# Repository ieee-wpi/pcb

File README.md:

# Essentials of PCB Design

[![CC BY-SA 4.0][cc-by-sa-shield]][cc-by-sa]

Project-oriented PCB design course taught at WPI. The course is a evening lecture series where students learn to layout and route an embedded system. Students then receive their boards and assemble them. The class was created by [Daniel Gorbunov](https://github.com/dgorbunov) and [Hubert Liu](https://github.com/124274sashimi) in 2024 and has been run every year since through the [IEEE WPI Student Branch](https://ieee.wpi.edu), which helps fund the class. You can reach us at [gr-pcb@wpi.edu](mailto:gr-pcb@wpi.edu) if you have questions.

### Lectures
| #  | Lecture				    |
| -- |-------- 				    |
| 01 | PCB Basics 		    |
| 02 | Project Design     |
| 03 | Layout + Routing   |
| 04 | Working with KiCad |

### Materials
| Folder      	  | Contents		            |
| --          	  |       -------- 			    |
| `datasheets`    | Datasheets for major parts  |
| `sample_board`  | Sample board design         |
| `slides`        | PDFs of slides	          	|
| `starter_board` | Starter template design     | 
| `code`        | Code examples	    |

### Lecture Recordings

> Note: To access the lecture recordings, you must sign in with a WPI account. This is WPI's policy for Echo360 recordings.

| Year  | Term  | Echo360      |
| ----- | ----- | ------------ |
| 2024 | A-Term | [Link](https://echo360.org/collection/4c2d5caf-a301-4c32-a2dd-bdd8c8c0b9d9/public) | 
| 2025 | A-Term | [Link](https://echo360.org/collection/bc2acf2f-69f2-4496-9638-cb1b12c30087/public) |
| 2026 | C-Term | [Link](https://echo360.org/collection/0ecf9c61-5003-4061-9b4f-ee87c14e6741/public) |

## Getting Started
Not sure where to get started on your design? You'll need to download and install [KiCad](https://www.kicad.org/download/). You'll also need the [Arduino IDE](https://www.arduino.cc/en/software) to program your board.

### Board
To get started on your own board design, navigate to [starter_board](https://github.com/IEEE-WPI/pcb/tree/main/starter_board) and read the instructions in the `README` file.

### Code
To get started uploading code to your board, navigate to [code](https://github.com/IEEE-WPI/pcb/tree/main/code) and read the instructions in the `README` file.

## License
This work is licensed under a
[Creative Commons Attribution-ShareAlike 4.0 International License][cc-by-sa].

[![CC BY-SA 4.0][cc-by-sa-image]][cc-by-sa]

[cc-by-sa]: http://creativecommons.org/licenses/by-sa/4.0/
[cc-by-sa-image]: https://licensebuttons.net/l/by-sa/4.0/88x31.png
[cc-by-sa-shield]: https://img.shields.io/badge/License-CC%20BY--SA%204.0-lightgrey.svg

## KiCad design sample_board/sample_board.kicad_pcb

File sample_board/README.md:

## Sample Board
This folder contains the sample board for the Track 1 design. We've ordered these boards to help demonstrate what the Track 1 boards will do. 

**If you're in Track 1, we encourage you not to look at the sample board files, but rather come up with your own layout and routing solutions**. The sample board by no means represents "the best" design for the board.

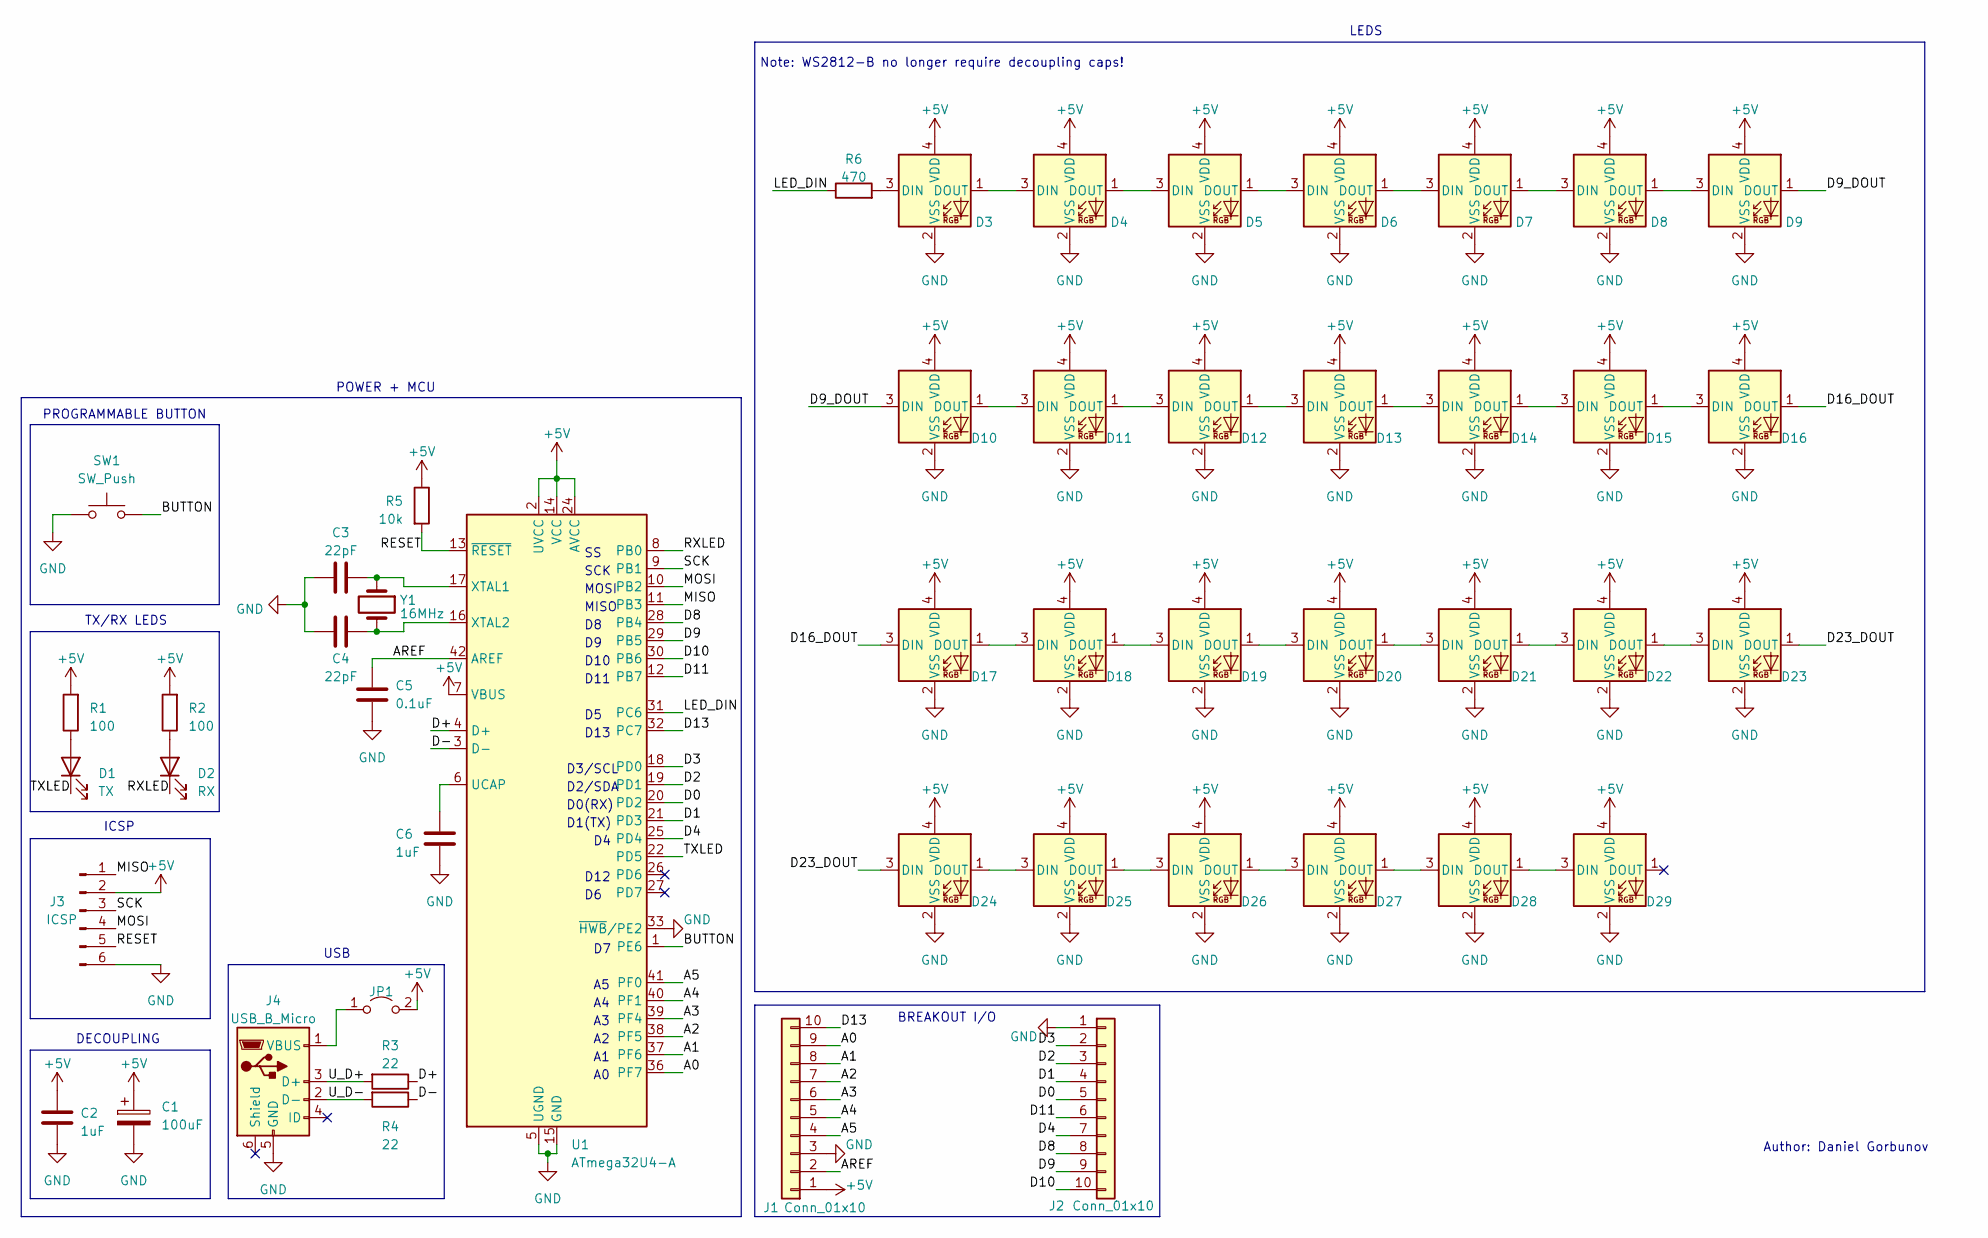
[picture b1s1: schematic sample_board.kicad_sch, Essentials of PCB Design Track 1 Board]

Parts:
C1: 100uF; CP_Elec_5x5.3
C2, C6: 1uF; C_0805_2012Metric_Pad1.18x1.45mm_HandSolder
C3, C4: 22pF; C_0805_2012Metric_Pad1.18x1.45mm_HandSolder
C5: 0.1uF; C_0805_2012Metric_Pad1.18x1.45mm_HandSolder
D1: TX; LED_0805_2012Metric_Pad1.15x1.40mm_HandSolder
D2: RX; LED_0805_2012Metric_Pad1.15x1.40mm_HandSolder
D3, D4, D5, D6, D7, D8, D9, D10, D11, D12, D13, D14, D15, D16, D17, D18, D19, D20, D21, D22, D23, D24, D25, D26, D27, D28, D29: SK6812MINI; LED_SK6812MINI_PLCC4_3.5x3.5mm_P1.75mm
J1, J2: Conn_01x10; PinHeader_1x10_P2.54mm_Vertical
J3: ICSP; PinHeader_2x03_P2.54mm_Vertical
J4: USB_B_Micro; USB_Micro-B_GCT_USB3076-30-A
JP1: Jumper_2_Open; SolderJumper-2_P1.3mm_Open_TrianglePad1.0x1.5mm
R1, R2: 100; R_0805_2012Metric_Pad1.20x1.40mm_HandSolder
R3, R4: 22; R_0805_2012Metric_Pad1.20x1.40mm_HandSolder
R5: 10k; R_0805_2012Metric_Pad1.20x1.40mm_HandSolder
R6: 470; R_0805_2012Metric_Pad1.20x1.40mm_HandSolder
SW1: SW_Push; SW_SPST_PTS647_Sx38
U1: ATmega32U4-A; TQFP-44_10x10mm_P0.8mm
Y1: 16MHz; Crystal_SMD_5032-2Pin_5.0x3.2mm

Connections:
+5V: C1.1, C2.1, D3.4 (VDD), D4.4 (VDD), D5.4 (VDD), D6.4 (VDD), D7.4 (VDD), D8.4 (VDD), D9.4 (VDD), D10.4 (VDD), D11.4 (VDD), D12.4 (VDD), D13.4 (VDD), D14.4 (VDD), D15.4 (VDD), D16.4 (VDD), D17.4 (VDD), D18.4 (VDD), D19.4 (VDD), D20.4 (VDD), D21.4 (VDD), D22.4 (VDD), D23.4 (VDD), D24.4 (VDD), D25.4 (VDD), D26.4 (VDD), D27.4 (VDD), D28.4 (VDD), D29.4 (VDD), J1.1, J3.2, JP1.2 (B), R1.2, R2.2, R5.1, U1.2 (UVCC), U1.7 (VBUS), U1.14 (VCC), U1.24 (AVCC), U1.34 (VCC), U1.44 (AVCC)
/A0: J1.9, U1.36 (PF7)
/A1: J1.8, U1.37 (PF6)
/A2: J1.7, U1.38 (PF5)
/A3: J1.6, U1.39 (PF4)
/A4: J1.5, U1.40 (PF1)
/A5: J1.4, U1.41 (PF0)
/AREF: C5.1, J1.2, U1.42 (AREF)
/BUTTON: SW1.2, U1.1 (PE6)
/D0: J2.5, U1.20 (PD2)
/D1: J2.4, U1.21 (PD3)
/D2: J2.3, U1.19 (PD1)
/D3: J2.2, U1.18 (PD0)
/D4: J2.7, U1.25 (PD4)
/D8: J2.8, U1.28 (PB4)
/D9: J2.9, U1.29 (PB5)
/D9_DOUT: D9.1 (DOUT), D10.3 (DIN)
/D10: J2.10, U1.30 (PB6)
/D11: J2.6, U1.12 (PB7)
/D13: J1.10, U1.32 (PC7)
/D16_DOUT: D16.1 (DOUT), D17.3 (DIN)
/D23_DOUT: D23.1 (DOUT), D24.3 (DIN)
/D+: R3.1, U1.4 (D+)
/D-: R4.1, U1.3 (D-)
/LED_DIN: R6.1, U1.31 (PC6)
/MISO: J3.1, U1.11 (PB3)
/MOSI: J3.4, U1.10 (PB2)
/RESET: J3.5, R5.2, U1.13 (~RESET)
/RXLED: D2.1 (K), U1.8 (PB0)
/SCK: J3.3, U1.9 (PB1)
/TXLED: D1.1 (K), U1.22 (PD5)
/U_D+: J4.3 (D+), R3.2
/U_D-: J4.2 (D-), R4.2
GND: C1.2, C2.2, C3.2, C4.2, C5.2, C6.2, D3.2 (VSS), D4.2 (VSS), D5.2 (VSS), D6.2 (VSS), D7.2 (VSS), D8.2 (VSS), D9.2 (VSS), D10.2 (VSS), D11.2 (VSS), D12.2 (VSS), D13.2 (VSS), D14.2 (VSS), D15.2 (VSS), D16.2 (VSS), D17.2 (VSS), D18.2 (VSS), D19.2 (VSS), D20.2 (VSS), D21.2 (VSS), D22.2 (VSS), D23.2 (VSS), D24.2 (VSS), D25.2 (VSS), D26.2 (VSS), D27.2 (VSS), D28.2 (VSS), D29.2 (VSS), J1.3, J2.1, J3.6, J4.5 (GND), SW1.1, U1.5 (UGND), U1.15 (GND), U1.23 (GND), U1.33 (~HWB/PE2), U1.35 (GND), U1.43 (GND)
unnamed: D1.2 (A), R1.1
unnamed: D2.2 (A), R2.1
unnamed: D3.3 (DIN), R6.2
unnamed: D3.1 (DOUT), D4.3 (DIN)
unnamed: D4.1 (DOUT), D5.3 (DIN)
unnamed: D5.1 (DOUT), D6.3 (DIN)
unnamed: D6.1 (DOUT), D7.3 (DIN)
unnamed: D7.1 (DOUT), D8.3 (DIN)
unnamed: D8.1 (DOUT), D9.3 (DIN)
unnamed: D10.1 (DOUT), D11.3 (DIN)
unnamed: D11.1 (DOUT), D12.3 (DIN)
unnamed: D12.1 (DOUT), D13.3 (DIN)
unnamed: D13.1 (DOUT), D14.3 (DIN)
unnamed: D14.1 (DOUT), D15.3 (DIN)
unnamed: D15.1 (DOUT), D16.3 (DIN)
unnamed: D17.1 (DOUT), D18.3 (DIN)
unnamed: D18.1 (DOUT), D19.3 (DIN)
unnamed: D19.1 (DOUT), D20.3 (DIN)
unnamed: D20.1 (DOUT), D21.3 (DIN)
unnamed: D21.1 (DOUT), D22.3 (DIN)
unnamed: D22.1 (DOUT), D23.3 (DIN)
unnamed: D24.1 (DOUT), D25.3 (DIN)
unnamed: D25.1 (DOUT), D26.3 (DIN)
unnamed: D26.1 (DOUT), D27.3 (DIN)
unnamed: D27.1 (DOUT), D28.3 (DIN)
unnamed: D28.1 (DOUT), D29.3 (DIN)
unnamed: J4.1 (VBUS), JP1.1 (A)
unnamed: C6.1, U1.6 (UCAP)
unnamed: C3.1, U1.17 (XTAL1), Y1.1
unnamed: C4.1, U1.16 (XTAL2), Y1.2

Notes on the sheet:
MOSI
D2/SDA
LEDS
D11
D3/SCL
USB
DECOUPLING
D1(TX)
D13
Note: WS2812-B no longer require decoupling caps!
Author: Daniel Gorbunov
PROGRAMMABLE BUTTON
MISO
D10
BREAKOUT I/O
POWER + MCU
TX/RX LEDS
ICSP
SCK
D12
D0(RX)

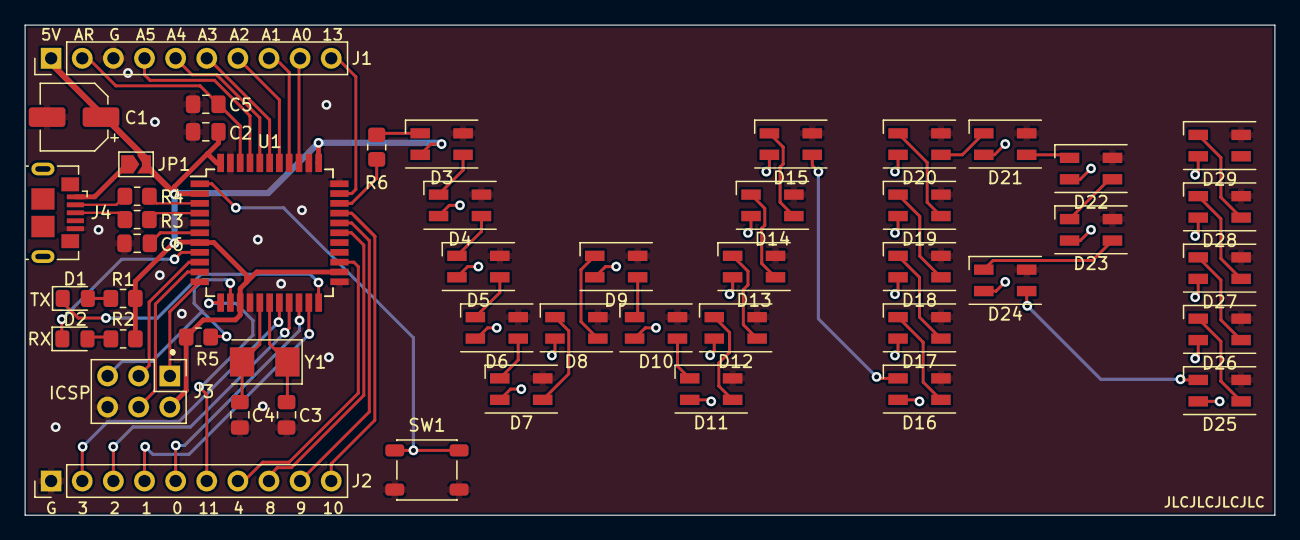
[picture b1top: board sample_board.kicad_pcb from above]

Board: 2 copper layers, 102.0 x 40.0 mm, 49 parts (0 on the bottom side), 64 nets.

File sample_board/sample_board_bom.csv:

"#","Reference","Qty","Value","Footprint","DNP"
"1","C1","1","100uF","Capacitor_SMD:CP_Elec_5x5.3",""
"2","C2, C6","2","1uF","Capacitor_SMD:C_0805_2012Metric_Pad1.18x1.45mm_HandSolder",""
"3","C3, C4","2","22pF","Capacitor_SMD:C_0805_2012Metric_Pad1.18x1.45mm_HandSolder",""
"4","C5","1","0.1uF","Capacitor_SMD:C_0805_2012Metric_Pad1.18x1.45mm_HandSolder",""
"5","D1","1","TX","LED_SMD:LED_0805_2012Metric_Pad1.15x1.40mm_HandSolder",""
"6","D2","1","RX","LED_SMD:LED_0805_2012Metric_Pad1.15x1.40mm_HandSolder",""
"7","D3, D4, D5, D6, D7, D8, D9, D10, D11, D12, D13, D14, D15, D16, D17, D18, D19, D20, D21, D22, D23, D24, D25, D26, D27, D28, D29","27","SK6812MINI","LED_SMD:LED_SK6812MINI_PLCC4_3.5x3.5mm_P1.75mm",""
"8","J1, J2","2","Conn_01x10","Connector_PinHeader_2.54mm:PinHeader_1x10_P2.54mm_Vertical",""
"9","J3","1","ICSP","Connector_PinHeader_2.54mm:PinHeader_2x03_P2.54mm_Vertical",""
"10","J4","1","USB_B_Micro","Connector_USB:USB_Micro-B_GCT_USB3076-30-A",""
"11","JP1","1","Jumper_2_Open","Jumper:SolderJumper-2_P1.3mm_Open_TrianglePad1.0x1.5mm",""
"12","R1, R2","2","100","Resistor_SMD:R_0805_2012Metric_Pad1.20x1.40mm_HandSolder",""
"13","R3, R4","2","22","Resistor_SMD:R_0805_2012Metric_Pad1.20x1.40mm_HandSolder",""
"14","R5","1","10k","Resistor_SMD:R_0805_2012Metric_Pad1.20x1.40mm_HandSolder",""
"15","R6","1","470","Resistor_SMD:R_0805_2012Metric_Pad1.20x1.40mm_HandSolder",""
"16","U1","1","ATmega32U4-A","Package_QFP:TQFP-44_10x10mm_P0.8mm",""
"17","Y1","1","16MHz","Crystal:Crystal_SMD_5032-2Pin_5.0x3.2mm",""

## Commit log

2024-09-21 move repo to org
2024-09-24 a-term lecture 1 slides
2024-09-24 cleanup stray gerber files
2024-09-25 cleanup
2024-09-25 reorg and update readme
2024-09-26 untrack kicad cache files
2024-09-26 add datasheets and new sample board files
2024-09-26 remove cached starter board files
2024-09-26 update board files for A24
2024-09-26 add d24 gerbers and update readme
2024-09-26 add design slides
2024-09-27 add gerbers
2024-09-27 update design slide with fixed image
2024-10-01 add READMEs to all folders
2024-10-01 update root readme with links
2024-10-01 fix readme links again
2024-10-01 add sample board readme
2024-10-01 update root README with starter links
2024-10-01 update starter code
2024-10-01 lock components
2024-10-01 layout and routing slides
2024-10-03 updated 3rd and 4th lecture slides
2024-10-06 sample board rev2; added button
2024-10-25 update lecture names in readme
2024-10-26 regenerate gerbers
2024-10-26 restore d24 board
2024-10-26 add colorful silkscreen board
2024-11-08 update flashlight code and add strobe
2024-12-08 Add CC license to README
2025-09-23 Add 2025 basics slides
2025-09-25 Add updated slides
2025-10-01 Add lecture 3 slides
2025-10-02 Add lecture 4 slides
2025-10-02 Add updated term to board
2026-02-15 Update first lecture slides
2026-02-16 Update slide
2026-02-20 Update 02 slides
2026-02-27 Update slides
2026-03-02 Update sample board for KiCad 9
2026-04-12 Update code with demo example
